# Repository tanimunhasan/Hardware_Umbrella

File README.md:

# Hardware_Umbrella
Printed Circuit Board Layout repository hosting to linkup

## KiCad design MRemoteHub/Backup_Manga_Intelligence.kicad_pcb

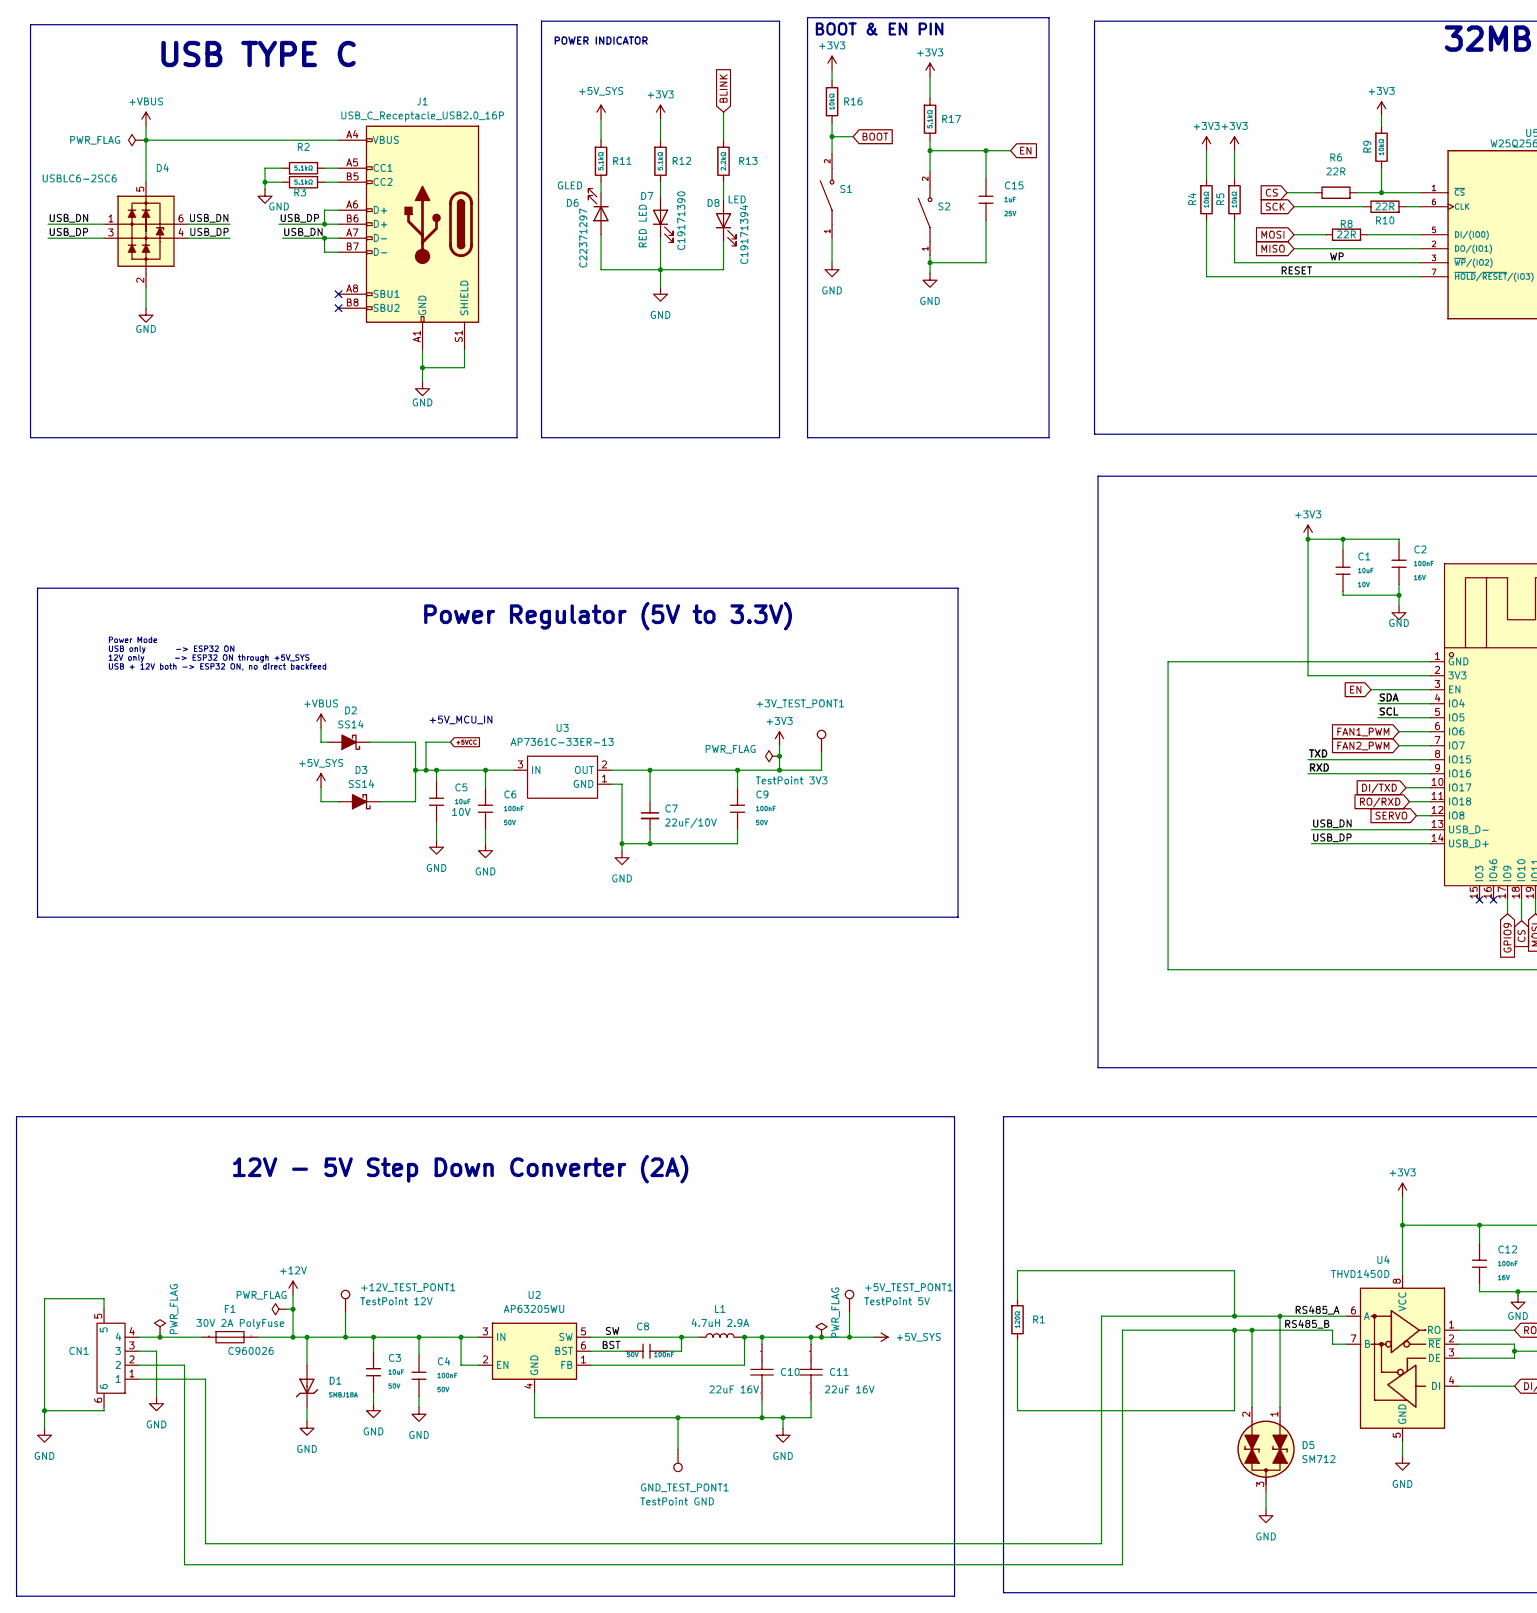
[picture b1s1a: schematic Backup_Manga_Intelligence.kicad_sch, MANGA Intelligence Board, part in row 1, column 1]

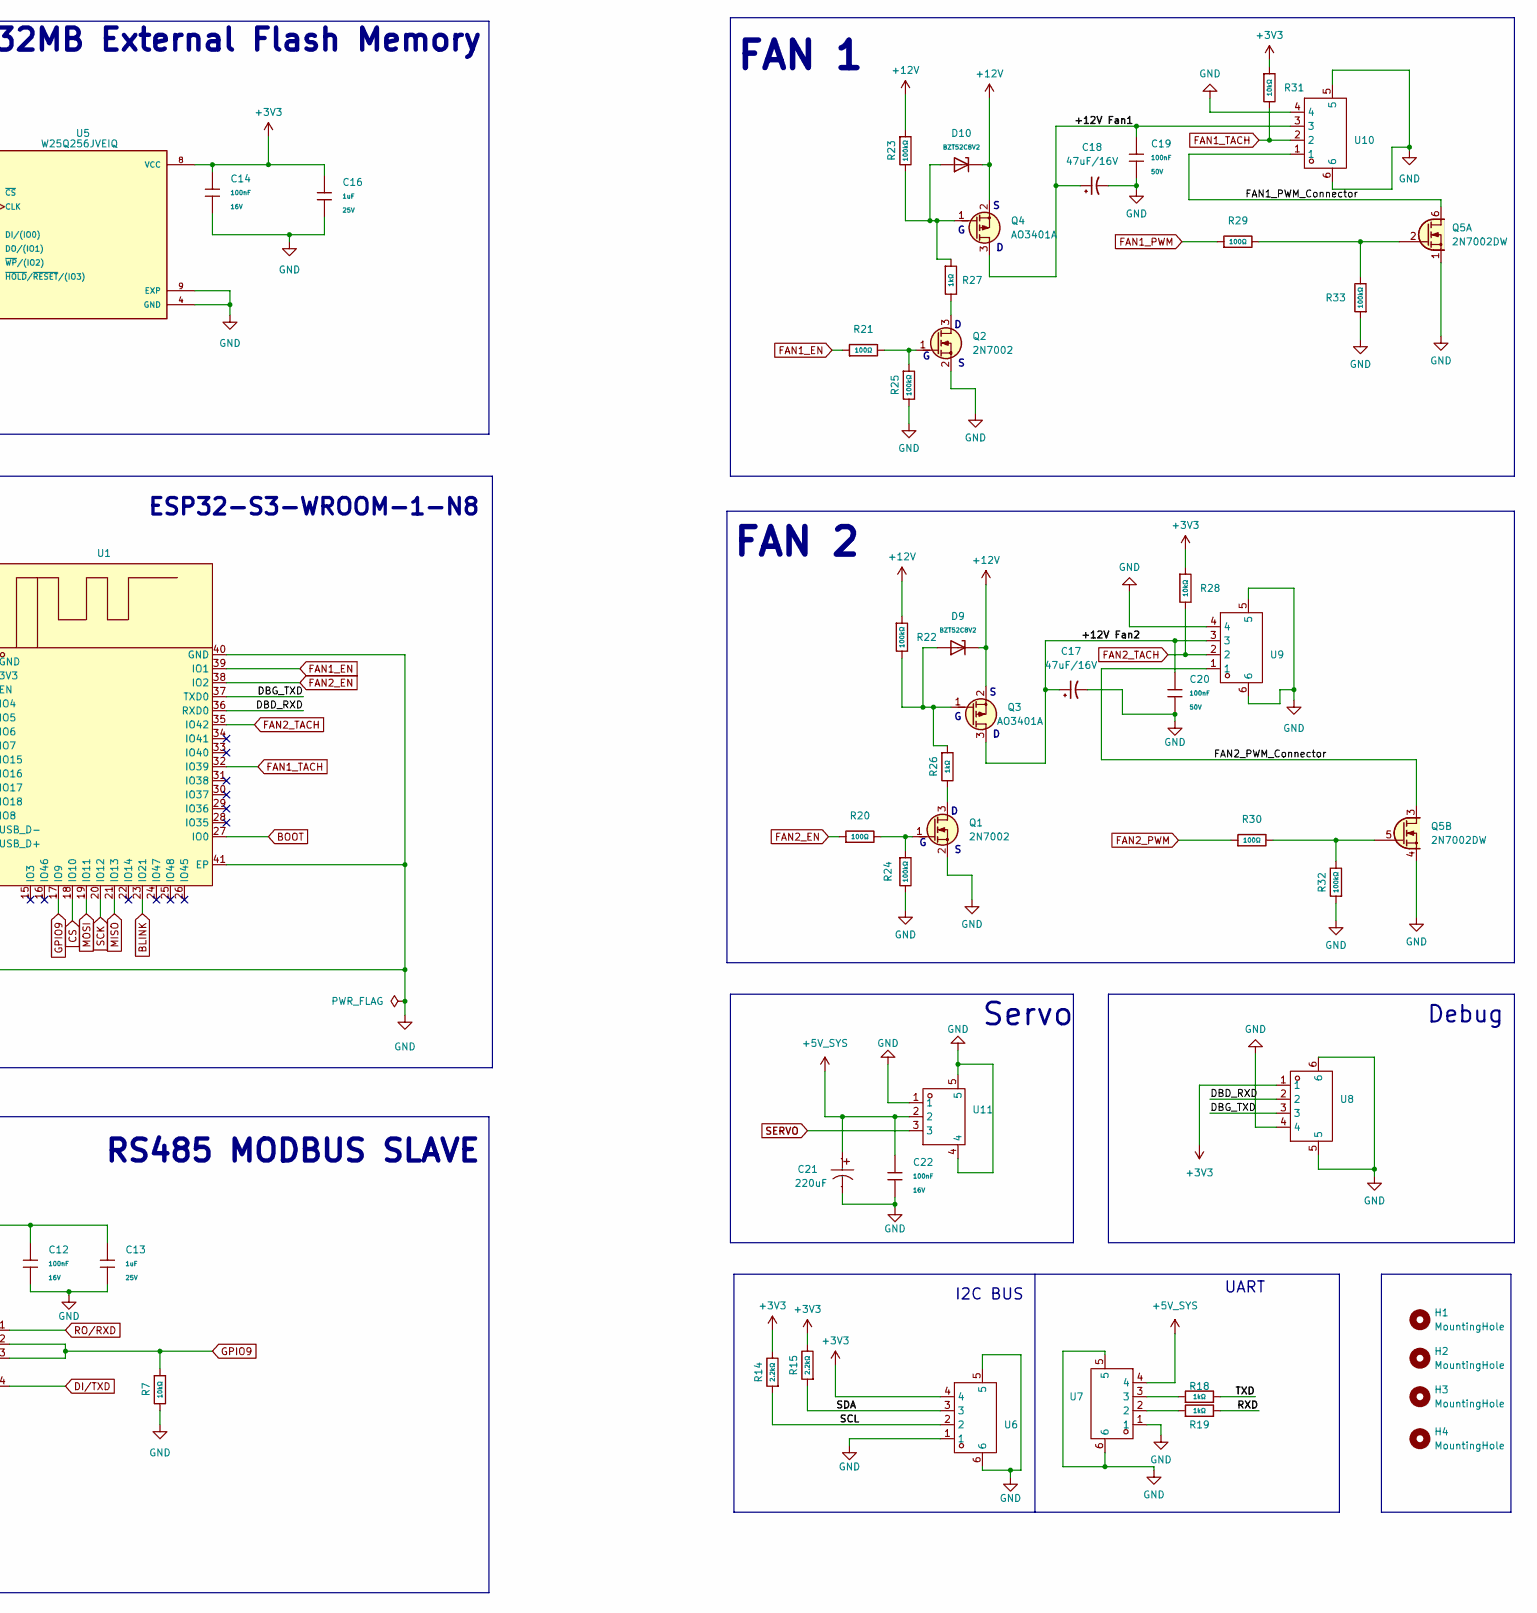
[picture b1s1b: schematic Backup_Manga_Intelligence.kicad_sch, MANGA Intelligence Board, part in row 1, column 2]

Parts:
+3V_TEST_PONT1: TestPoint 3V3; TestPoint_Pad_D1.0mm
+5V_TEST_PONT1: TestPoint 5V; TestPoint_Pad_D1.0mm
+12V_TEST_PONT1: TestPoint 12V; TestPoint_Pad_D1.0mm
C1: 10uF; C_0603; Voltage Rated 10V; Tolerance ±10%; Part CL10A106KP8NNNC; LCSC C19702
C2, C12, C14, C22: 100nF; C_0402; Voltage Rated 16V; Tolerance ±10%; Part CL05B104KO5NNNC; LCSC C1525
C3: 10uF; C_0805; Voltage Rated 50V; Tolerance ±10%; Part GRM21BR61H106KE43L; LCSC C440198
C4, C19, C20: 100nF; C_0402; Voltage Rated 50V; Tolerance ±10%; Part CL05B104KB54PNC; LCSC C307331
C5: 10uF; C_0805; Voltage Rated 10V; LCSC Part # C17024
C6, C8, C9: 100nF; C_0603; Voltage Rated 50V; Tolerance ±10%; Part CC0603KRX7R9BB104; LCSC C14663
C7: 22uF; C_0805_2012Metric; Part Number LMK212BBJ226MG-T; JLCPCB ID C45783
C10, C11: 22uF 16V; C1210; Manufacturer Part CL32B226KOJNNNE; LCSC Part Name 22uF ±10% 16V
C13, C15, C16: 1uF; C_0402; Voltage Rated 25V; Tolerance ±10%; Part CL05A105KA5NQNC; LCSC C52923
C17, C18: 47uF_5x5.3_16V; CP_Elec_3x5.3; Part Number VE-470M1CTR-0505; JLCPCB ID C134798
C21: 220uF; CAP-SMD_BD6.3-L6.6-W6.6-FD; Manufacturer Part RVT1A221M0605; LCSC Part Name 220uF ±20% 10V
CN1: CONN-SMD_4P-P1.25_53261-0471; Manufacturer Part 532610471; LCSC Part Name 1x4P 间距:1.25mm 卧贴 系列:PicoBlade(MX 1.25)
D1: SMBJ18A; D_SMB; Part SMBJ18A; LCSC C19077573
D2, D3: SS14; D_SMA
D4: USBLC6-2SC6; SOT-23-6
D5: SM712; SOT-23; LCSC Part # C404012
D6: GLED; LED_0603_1608Metric; LCSC Part # C22371297
D7: RED LED; LED_0603_1608Metric; LCSC Part # C19171390
D8: LED; LED_0603_1608Metric; LCSC Part # C19171394
D9, D10: BZT52C8V2; D_SOD-123; Part BZT52C8V2; LCSC C19077406
F1: 30V 2A PolyFuse; F1812; Manufacturer Part BSMD1812-200-30V; LCSC Part Name 30V 2A 1812自恢复
GND_TEST_PONT1: TestPoint GND; TestPoint_Pad_D1.0mm
H1, H2, H3, H4: MountingHole; MountingHole_3.2mm_M3_DIN965_Pad
J1: USB_C_Receptacle_USB2.0_16P; USB-C-SMD_HCTL_HC-TYPE-C-16P-01M
L1: 4.7uH 2.9A; L_APV_ANR4020; LCSC C135270
Q1, Q2: 2N7002; SOT-23
Q3, Q4: AO3401A; SOT-23
Q5: 2N7002DW; SOT-363_SC-70-6
R1: 120Ω; R_0402; Overload Voltage (Max) 50V; Tolerance ±1%; Part 0402WGF1200TCE; LCSC C25079
R2, R3, R11, R12, R17: 5.1kΩ; R_0402; Overload Voltage (Max) 50V; Tolerance ±1%; Part 0402WGF5101TCE; LCSC C25905
R4, R5, R7, R9, R16, R28, R31: 10kΩ; R_0402; Overload Voltage (Max) 50V; Tolerance ±1%; Part 0402WGF1002TCE; LCSC C25744
R6: 22R; R_0402_1005Metric
R8, R10: 22R; R_0402
R13, R14, R15: 2.2kΩ; R_0402; Overload Voltage (Max) 50V; Tolerance ±1%; Part 0402WGF2201TCE; LCSC C25879
R18, R19, R26, R27: 1kΩ; R_0402; Overload Voltage (Max) 50V; Tolerance ±1%; Part 0402WGF1001TCE; LCSC C11702
R20, R21, R29, R30: 100Ω; R_0603; Overload Voltage (Max) 75V; Tolerance ±1%; Part 0603WAF1000T5E; LCSC C22775
R22, R23, R24, R25, R32, R33: 100kΩ; R_0402; Overload Voltage (Max) 50V; Tolerance ±1%; Part 0402WGF1003TCE; LCSC C25741
S1, S2: TS-1088-AR02016; SW_TS-1088-AR02016; PARTREV N/A
U1: 2.4GHz; WIFIM-SMD_ESP32-S3-WROOM-1-N8; Manufacturer Part ESP32-S3-WROOM-1-N8; LCSC Part Name 不带固件 通用型Wi-Fi+低功耗蓝牙MCU模组
U2: AP63205WU; TSOT-23-6
U3: AP7361C-33ER-13; SOT-223-3_L6.5-W3.4-P2.30-LS7.0-BR-1; Manufacturer Part AP7361C-33ER-13; LCSC Part Name 输入6V 输出3.3V 1A
U4: THVD1450D; SOIC-8_3.9x4.9mm_P1.27mm
U5: W25Q256JVEIQ; PARTREV Q
U6, U7, U8, U9, U10: CONN-SMD_4P-P1.00_MEGASTAR_ZX-SH1.0-4PWT; Manufacturer Part ZX-SH1.0-4PWT; LCSC Part Name 1x4P 间距:1mm 卧贴 系列:SH
U11: CONN-SMD_3P-P1.00_MEGASTAR_ZX-SH1.0-3PWT; Manufacturer Part ZX-SH1.0-3PWT; LCSC Part Name 1x3P 间距:1mm 卧贴 系列:SH

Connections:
+3V3: +3V_TEST_PONT1.1, C1.1, C2.1, C7.1, C9.1, C12.1, C13.1, C14.1, C16.1, R4.1, R5.1, R9.1, R12.1, R14.2, R15.2, R16.1, R17.1, R28.1, R31.1, U1.2 (3V3), U3.2 (OUT), U4.8 (VCC), U5.8 (VCC), U6.4, U8.1
+5VCC: C5.1, C6.1, D2.1 (K), D3.1 (K), U3.3 (IN)
+5V_SYS: +5V_TEST_PONT1.1, C10.1, C11.1, C21.1, C22.1, D3.2 (A), L1.2, R11.1, U2.1 (FB), U7.4, U11.2
+12V: +12V_TEST_PONT1.1, C3.1, C4.1, D1.2, D9.1, D10.1, F1.2, Q3.2 (S), Q4.2 (S), R22.1, R23.1, U2.2 (EN), U2.3 (IN)
+VBUS: D2.2 (A), D4.5 (VP), J1.A4 (VBUS), J1.A9 (VBUS), J1.B4 (VBUS), J1.B9 (VBUS)
/+12V Fan1: C18.1, C19.1, Q4.3 (D), U10.3
/+12V Fan2: C17.1, C20.1, Q3.3 (D), U9.3
/BST: C8.1, U2.6 (BST)
/DBD_RXD: U1.36 (RXD0), U8.2
/DBG_TXD: U1.37 (TXD0), U8.3
/FAN1_PWM_Connector: Q5.6 (D1), U10.1
/FAN2_PWM_Connector: Q5.3 (D2), U9.1
/RESET: R4.2, U5.7 (~HOLD/~RESET/(IO3))
/RS485_A: CN1.1, D5.1 (A1), R1.1, U4.6 (A)
/RS485_B: CN1.2, D5.2 (A2), R1.2, U4.7 (B)
/RXD: R19.2, U1.9 (IO16)
/SCL: R14.1, U1.5 (IO5), U6.2
/SDA: R15.1, U1.4 (IO4), U6.3
/SW: C8.2, L1.1, U2.5 (SW)
/TXD: R18.2, U1.8 (IO15)
/USB_DN: D4.1 (L1), D4.6 (L1), J1.A7 (D-), J1.B7 (D-), U1.13 (USB_D-)
/USB_DP: D4.3 (L2), D4.4 (L2), J1.A6 (D+), J1.B6 (D+), U1.14 (USB_D+)
/WP: R5.2, U5.3 (~WP/(IO2))
BLINK: R13.1, U1.23 (IO21)
BOOT: R16.2, S1.2, U1.27 (IO0)
CS: R6.1, U1.18 (IO10)
DI/TXD: U1.10 (IO17), U4.4 (DI)
EN: C15.1, R17.2, S2.2, U1.3 (EN)
FAN1_EN: R21.1, U1.39 (IO1)
FAN1_PWM: R29.1, U1.6 (IO6)
FAN1_TACH: R31.2, U1.32 (IO39), U10.2
FAN2_EN: R20.1, U1.38 (IO2)
FAN2_PWM: R30.1, U1.7 (IO7)
FAN2_TACH: R28.2, U1.35 (IO42), U9.2
GND: C1.2, C2.2, C3.2, C4.2, C5.2, C6.2, C7.2, C9.2, C10.2, C11.2, C12.2, C13.2, C14.2, C15.2, C16.2, C17.2, C18.2, C19.2, C20.2, C21.2, C22.2, CN1.3, CN1.5, CN1.6, D1.1, D4.2 (VN), D5.3 (Com), D6.2 (A), D7.1 (K), D8.1 (K), GND_TEST_PONT1.1, J1.A1 (GND), J1.A12 (GND), J1.B1 (GND), J1.B12 (GND), J1.S1 (SHIELD), Q1.2 (S), Q2.2 (S), Q5.1 (S1), Q5.4 (S2), R2.1, R3.2, R7.2, R24.2, R25.2, R32.1, R33.1, S1.1, S2.1, U1.1 (GND), U1.40 (GND), U1.41 (EP), U2.4 (GND), U3.1 (GND), U4.5 (GND), U5.4 (GND), U5.9 (EXP), U6.1, U6.5, U6.6, U7.1, U7.5, U7.6, U8.4, U8.5, U8.6, U9.4, U9.5, U9.6, U10.4, U10.5, U10.6, U11.1, U11.4, U11.5
GPIO9: R7.1, U1.17 (IO9), U4.2 (~RE), U4.3 (DE)
MISO: U1.21 (IO13), U5.2 (DO/(IO1))
MOSI: R8.1, U1.19 (IO11)
unnamed: CN1.4, F1.1
unnamed: D6.1 (K), R11.2
unnamed: D7.2 (A), R12.2
unnamed: D8.2 (A), R13.2
unnamed: J1.A5 (CC1), R2.2
unnamed: J1.B5 (CC2), R3.1
unnamed: Q1.3 (D), R26.2
unnamed: Q1.1 (G), R20.2, R24.1
unnamed: Q2.3 (D), R27.2
unnamed: Q2.1 (G), R21.2, R25.1
unnamed: D9.2, Q3.1 (G), R22.2, R26.1
unnamed: D10.2, Q4.1 (G), R23.2, R27.1
unnamed: Q5.2 (G1), R29.2, R33.2
unnamed: Q5.5 (G2), R30.2, R32.2
unnamed: R18.1, U7.3
unnamed: R19.1, U7.2
unnamed: R10.2, U5.6 (CLK)
unnamed: R8.2, U5.5 (DI/(IO0))
unnamed: R6.2, R9.2, U5.1 (~CS)
RO/RXD: U1.11 (IO18), U4.1 (RO)
SCK: R10.1, U1.20 (IO12)
SERVO: U1.12 (IO8), U11.3

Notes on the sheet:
FAN 2
I2C BUS
POWER INDICATOR
UART
Power Mode USB only -> ESP32 ON 12V only -> ESP32 ON through +5V_SYS USB + 12V both -> ESP32 ON, no direct backfeed
Power Regulator (5V to 3.3V)
FAN 1
12V - 5V Step Down Converter (2A)
USB TYPE C
Debug
ESP32-S3-WROOM-1-N8
RS485 MODBUS SLAVE
+5V_MCU_IN
Servo
32MB External Flash Memory
BOOT & EN PIN

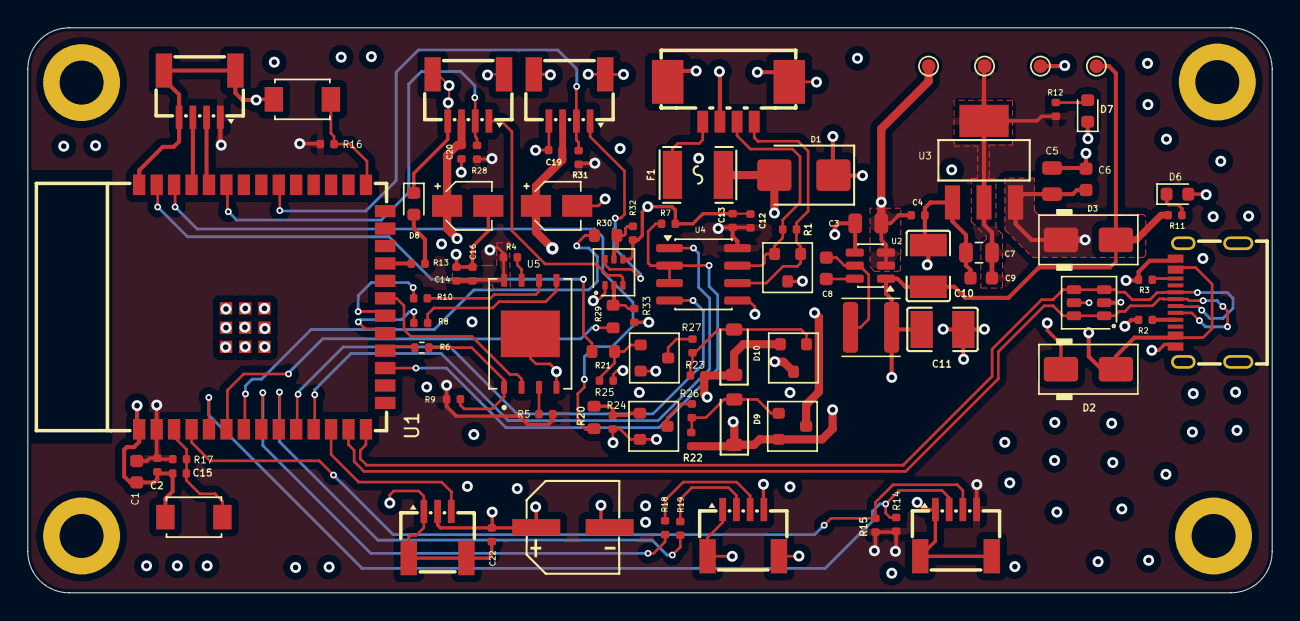
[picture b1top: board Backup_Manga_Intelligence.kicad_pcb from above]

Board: 4 copper layers, 90.6 x 41.1 mm, 95 parts (0 on the bottom side), 60 nets.

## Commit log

2026-06-28 Added
2026-06-28 Updated Text Box EN BOOT
